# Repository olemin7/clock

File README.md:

# platformio
source ~/.platformio/penv/bin/activate
pio project init --ide eclipse
# clock
clock with ntp synk
# Board
http://arduino.esp8266.com/stable/package_esp8266com_index.json
# lib 
https://github.com/olemin7/esp_libs

# referenses
schematic: https://circuits.io/circuits/3798057-net-clock-led
gtest
https://www.codeproject.com/Articles/811934/Cplusplus-unit-test-start-guide-how-to-set-up-Goog
https://github.com/google/googletest.git
arduino:
https://github.com/arduino/Arduino/blob/master/build/shared/manpage.adoc

# esp8266 reference
http://www.kloppenborg.net/blog/microcontrollers/2016/08/02/getting-started-with-the-esp8266

##wemos
Pin | Function    | ESP-8266 Pin | used
TX  | TXD         | TXD          |
RX  | RXD         | RXD          |
A0  | ADC, 3.3V   | A0           | photoresistor
D0  | IO          | GPIO16       |
D1  | IO, SCL     | GPIO5        | LedStript.in
D2  | IO, SDA     | GPIO4        | WallSwitch.out
D3  | IO, 10k P-up| GPIO0        | IRsensor.OUT
D4  | IO, 10k P-up,LED|   GPIO2  | DHT.data
D5  | IO, SCK     | GPIO14       | MAX7219.CLK
D6  | IO, MISO    | GPIO12       | MAX7219.CS
D7  | IO, MOSI    | GPIO13       | MAX7219.DIN
D8  | IO, 10k P-down, SS|  GPIO15|
G   | Ground      | GND          |
5V  | 5V          | -            |
3V3 | 3.3V        | 3.3V         |
RST | Reset       | RST          |

#ADC wemos
 A0--
    |
   220K
    |--- ADC
   100K
    |
   GND
 
#photoresistor
(+3.3) -termistor- (A0) -resistor 10k- (GND)

#DHT
1 vcc (3.3V)
2 data (D4)
3 nc
4 GND (G)

#Display MAX7219
1 VCC (+5v)
2 GND
3 DIN (MOSI,D7)
4 CS (D6) !??D6 is MISO can it be used as GPO when SPI enabled? 
5 CLK (SCK,D5)

#IRsensor 
(see from front)
out (D3)
gnd
vcc

#WallSwitch
out (D2)

#LedStript
in (D1)
 
https://github.com/adam-p/markdown-here/wiki/Markdown-Cheatsheet#lists

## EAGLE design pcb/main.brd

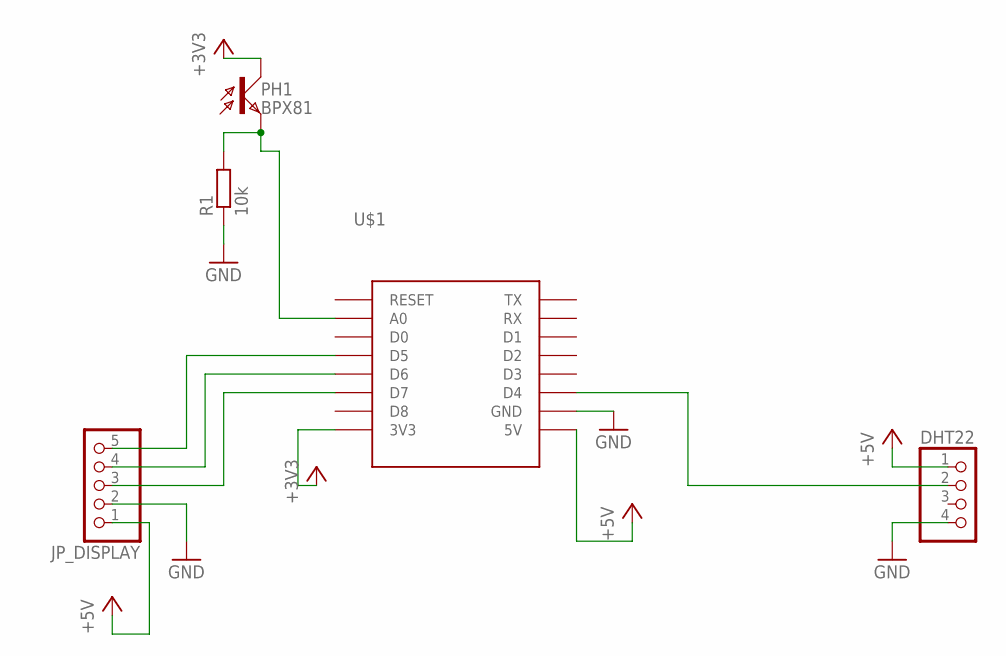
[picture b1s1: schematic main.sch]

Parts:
DHT22: PINHD-1X4/90; 1X04/90
JP_DISPLAY: PINHD-1X5/90; 1X05/90
PH1: BPX81
R1: 10k; R0805
U$1: WEMOS-D1-MINI

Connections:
+3V3: PH1.C, U$1.3V3
+5V: DHT22.1, JP_DISPLAY.1, U$1.5V
GND: DHT22.4, JP_DISPLAY.2, R1.1, U$1.GND
unnamed: PH1.E, R1.2, U$1.A0
unnamed: DHT22.2, U$1.D4
unnamed: JP_DISPLAY.3, U$1.D7
unnamed: JP_DISPLAY.4, U$1.D6
unnamed: JP_DISPLAY.5, U$1.D5

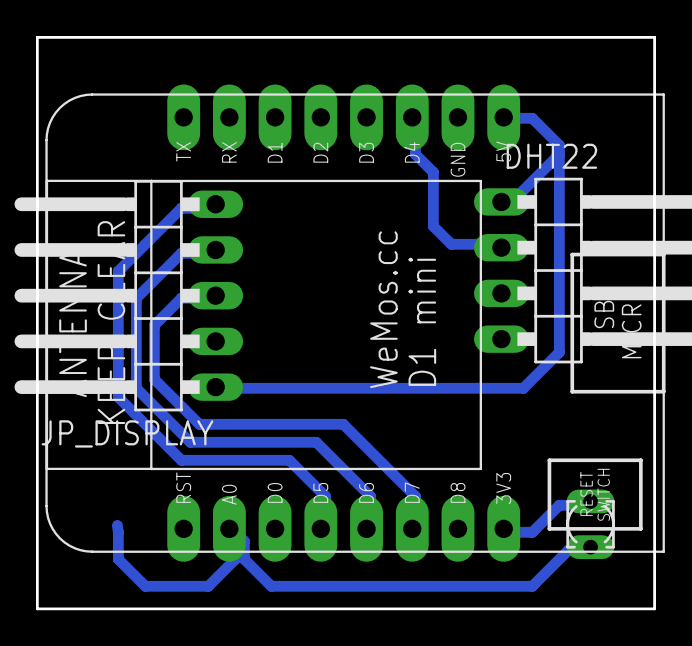
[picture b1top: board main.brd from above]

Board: 2 copper layers, 34.3 x 31.8 mm, 5 parts (1 on the bottom side), 8 nets.

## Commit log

2017-02-11 added LDR
2017-02-12 rtc wraper to work with epoc time
2017-02-14 add make file
2017-02-14 +asink ntp time read
2017-02-16 synk time and timezones
2017-02-17 clock str separated
2017-02-17 fix start up +intensivity
2017-02-17 add font
2017-03-22 fix font
2017-03-24 update for creating tests
2017-03-24 intens
2017-03-24 ajust values intensivity
2017-03-24 comtiled time in utc now
2017-04-21 web update draft
2017-04-22 sanitary
2017-04-22 add arduino ota
2017-04-23 ota moved to libpack
2017-04-25 update library lists
2017-04-30 refactoring
2017-05-02 fix connectin
2017-05-20 migrated on sloeber
2017-05-21 ota , sensor updatetd
2017-05-25 ugrade ntp time synk
2017-05-28 annd hw rtc switch (if present)
2017-05-28 add setting host name
2017-06-01 move CIntensity to libpack
2017-06-04 add loop intensivity
2017-06-09 move cmqtt to lib pack'
2017-07-27 move wifi loop
2017-09-24 refactor use observer pattern
2017-12-06 add led ir control, update observers
2017-12-17 prerelease checking + fix ir start
2017-12-18 fixed led part
2018-11-28 migrate on eclipse + inline some libs
2018-11-28 releif from filters
2018-11-30 set low spi spid for max7219
2018-12-02 six update client
2018-12-03 add delay in max72 cs pulse
2018-12-05 add delay after spi sent, update display when minutes are different
2018-12-05 test home
2019-01-17 upd docs
2019-01-17 upd led doc
2019-01-30 add status page, abbility to exclude unused module
2019-02-02 upd frequense dobouce +wifi reboot...
2019-03-05 set rotation for new screan
2019-03-20 en mqtt
2020-03-17 upd pio
2020-12-30 renew
2021-01-01 littlesf beg
2021-01-02 fix build
2021-01-02 upd ir lib
2021-01-03 signal
2021-01-03 led handler
2021-01-07 upd ui
2021-01-08 cmd from ui
2021-01-09 ger rc code
2021-01-14 fix ap
2021-01-14 beg decode
2021-01-16 save mode + config
2021-01-24 mqtt cb
2021-01-25 add led cmd mqtt
2021-01-26 exclusive ir conf
2021-01-27 logs
2021-01-27 up ui
2021-01-27 web log
2021-01-27 upd log
2021-03-16 ntp , no swich, mqtt itle
2021-04-28 upd ldr range
2021-05-01 upd config
2021-05-13 signal on change
2021-05-13 dit structure
2021-05-13 upd signal
2023-12-06 power event
2024-02-26 ntp port randomiser
